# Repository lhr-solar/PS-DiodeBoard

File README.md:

# PS-DiodeBoard
Diode for preventing reverse current on the inputs of the power board

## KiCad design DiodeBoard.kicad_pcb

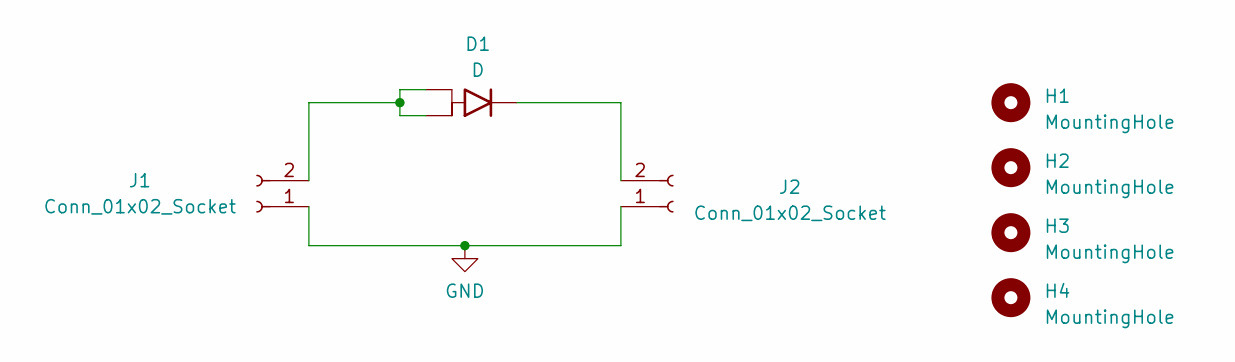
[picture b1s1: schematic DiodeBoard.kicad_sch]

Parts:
D1: D; SBLB25L30CTE345
H1, H2, H3, H4: MountingHole; MountingHole_3mm
J1, J2: Conn_01x02_Socket; Molex_Sabre_43160-0102_1x02_P7.49mm_Vertical

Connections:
GND: J1.1, J2.1
unnamed: D1.3 (K), J2.2
unnamed: D1.1 (A), D1.2 (A), J1.2

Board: 2 copper layers, 7 parts (0 on the bottom side), 3 nets, no tracks yet.
